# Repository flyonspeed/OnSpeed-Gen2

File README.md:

# OnSpeed-Gen2
Gen2 - OnSpeed open source hardware and software

This is a device that provides simple and intuitive Onspeed tone cues that allow the pilot to hear key performance AOA's as well outstanding progressive stall warning. ONSPEED AOA is used for approach and landing, assists with maximum performance takeoff and provides optimum turn performance.  The aural logic simplifies energy management and helps the pilot maintain positive aircraft control.

The current Gen2 device is avionics independent. The current features include:

    Measures differential pressures from an AOA pitot tube
  
    Measures static pressure
  
    Receives, parses and logs several types of EFIS data for testing purposes
  
    Receives, parses and logs flight test boom data for testing purposes
  
    Calculates a differential pressure based calibrated Angle of Attack and uses it to generate the OnSpeed tones.
  
    Can be wired directly into the aircraft's audio panel.
  
    It logs all data at 50Hz to the onboard SD card and provides an experimental AOA display via its Wifi interface.
  
    Logs can also be downloaded via Wifi.

We are happy to collaborate and answer any questions.  We will work with any experimenter or manufacturer that is interested in adapting the logic and always welcome qualified volunteers that want to join the project. Email us at team@flyonspeed.org to get in touch.

More details and videos of the OnSpeed system at http://flyOnspeed.org

**OnSpeed Gen2 System Diagram:**

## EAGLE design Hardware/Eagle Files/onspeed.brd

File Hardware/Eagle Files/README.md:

This folder contains the Onspeed Eagle files. Schematic and board files are also available in PDF form.\
\
**Note: We didn't end up using the Eagle .brd file. Board was rerouted in Altium. Gerber files and PDF of the board are in the Board Files folder**

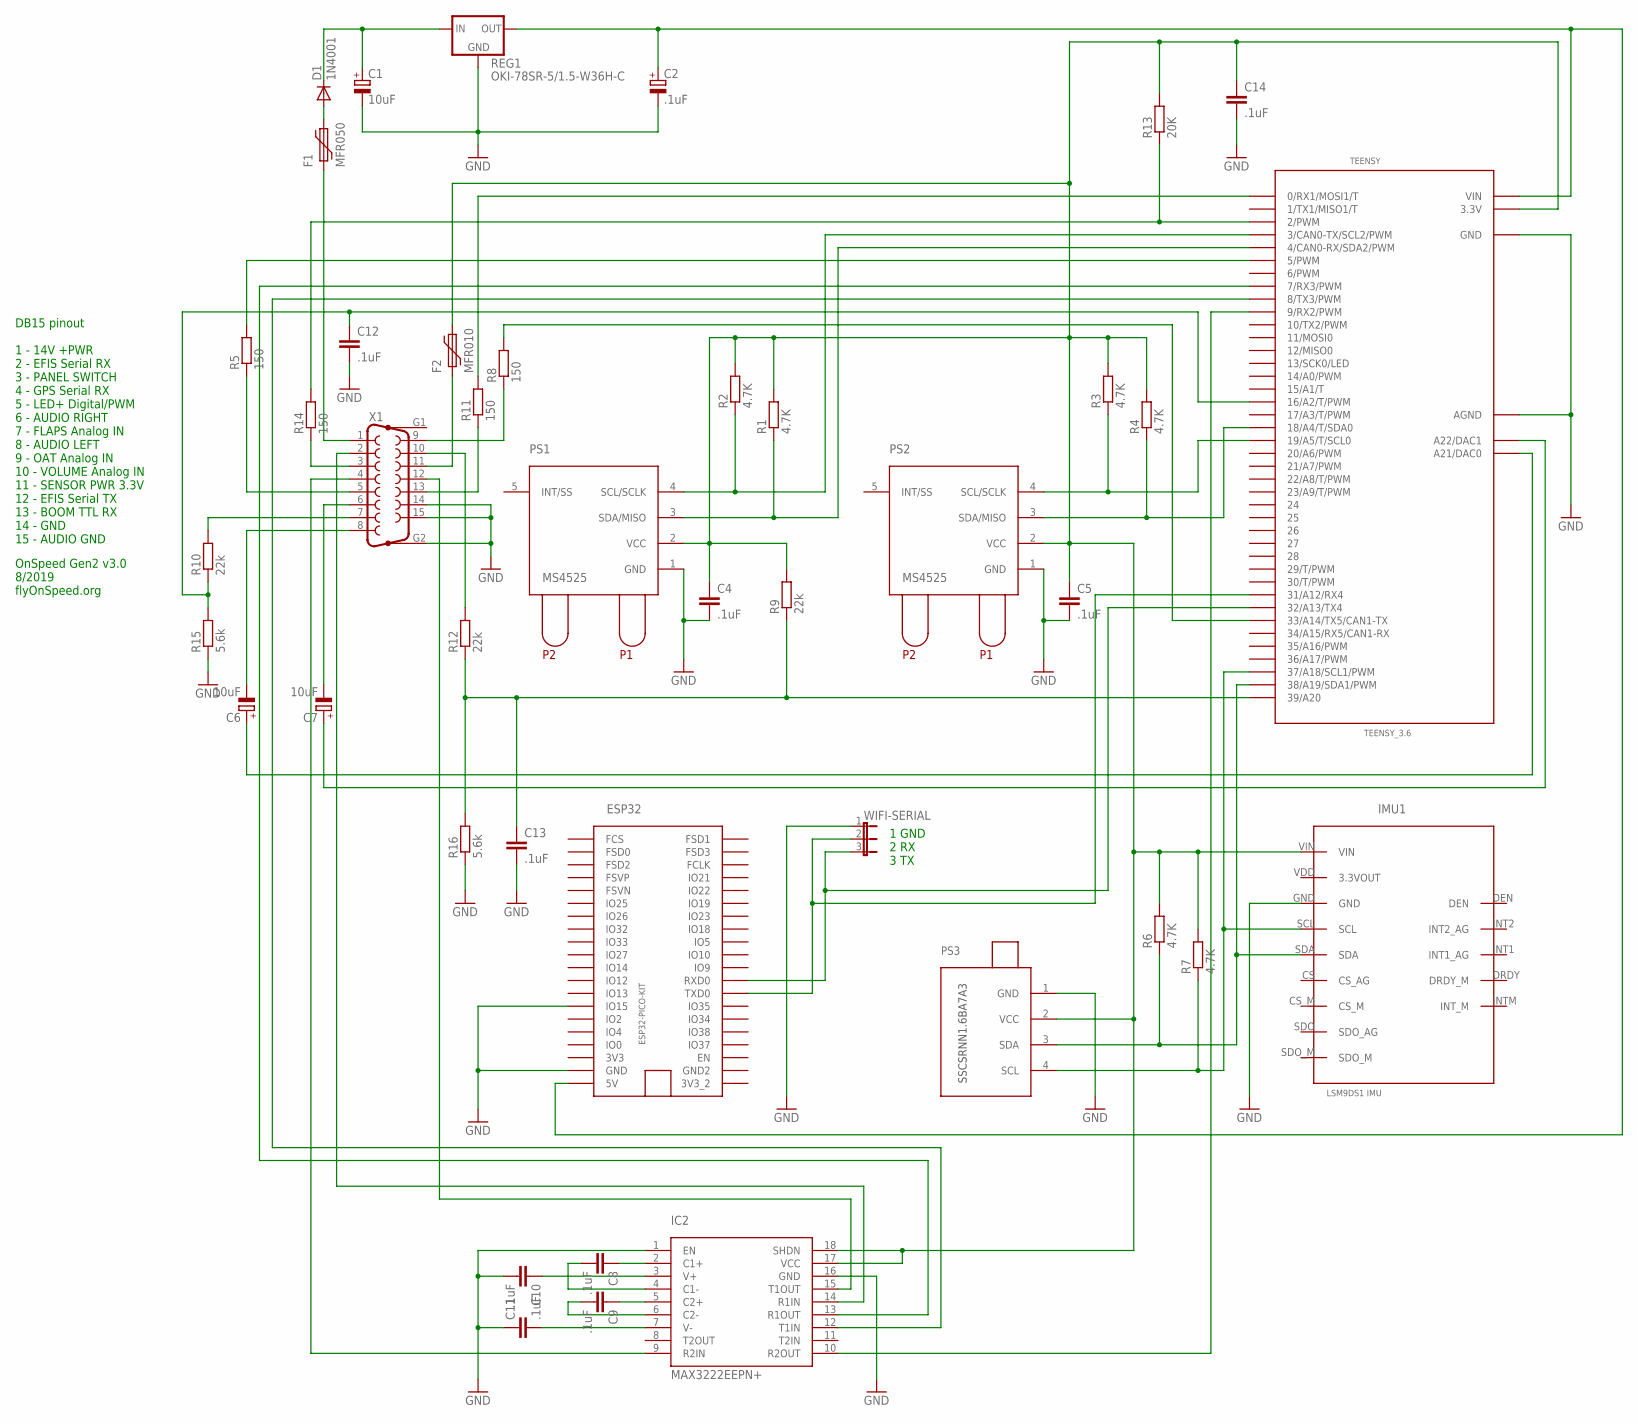
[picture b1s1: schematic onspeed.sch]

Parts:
C1, C6, C7: 10uF; E2-5
C2: .1uF; E2-5
C4, C5, C8, C9, C10, C11, C12, C13, C14: .1uF; C025-025X050
D1: 1N4001; DO41-10
ESP32: ESP32-PICO-KIT; ESP32PICOKIT
F1: MFR050; MF-5,1B
F2: MFR010; MF-5,1B
IC2: MAX3222EEPN+; DIL18
IMU1: LSM9DS1 IMU; LSM9DS1_BREAKOUT
PS1, PS2: MS4525; DIL08-500
PS3: SSCSRNN1.6BA7A3; SIP-RN
R1, R2, R3, R4, R6, R7: 4.7K; 0207/10
R5, R8, R11, R14: 150; 0207/10
R9, R10, R12: 22k; 0207/10
R13: 20K; 0207/10
R15, R16: 5.6k; 0207/10
REG1: OKI-78SR-5/1.5-W36H-C; SIP3H
TEENSY: TEENSY_3.6; TEENSY_3.6_DIL
WIFI-SERIAL: JP2E; JP2
X1: F15HP

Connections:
GND: C1.-, C2.-, C4.2, C5.2, C10.2, C11.1, C12.2, C13.2, C14.2, ESP32.P$GND (GND), ESP32.P$IO15 (IO15), IC2.1 (EN), IC2.16 (GND), IMU1.GND, PS1.1 (GND), PS2.1 (GND), PS3.1 (GND), R15.1, R16.1, REG1.2 (GND), TEENSY.AGND, TEENSY.GND, TEENSY.GND1 (GND), WIFI-SERIAL.1, X1.14, X1.15, X1.G2
unnamed: C1.+, D1.C, REG1.1 (IN)
unnamed: IC2.15 (T1OUT), X1.12
unnamed: R12.2, X1.10
unnamed: C2.+, ESP32.P$5V (5V), REG1.3 (OUT), TEENSY.VIN
unnamed: C12.1, R10.1, R15.2, TEENSY.16/A2 (16/A2/T/PWM)
unnamed: C7.-, X1.6
unnamed: R5.2, TEENSY.5 (5/PWM)
unnamed: IC2.12 (T1IN), TEENSY.8 (8/TX3/PWM)
unnamed: ESP32.P$RXD0 (RXD0), TEENSY.32/A13 (32/A13/TX4), WIFI-SERIAL.3
unnamed: ESP32.P$TXD0 (TXD0), TEENSY.31/A12 (31/A12/RX4), WIFI-SERIAL.2
unnamed: IC2.9 (R2IN), X1.4
unnamed: R11.2, TEENSY.0 (0/RX1/MOSI1/T)
unnamed: IC2.14 (R1IN), X1.2
unnamed: IC2.10 (R2OUT), TEENSY.9 (9/RX2/PWM)
unnamed: C7.+, TEENSY.A22 (A22/DAC1)
unnamed: PS1.4 (SCL/SCLK), R2.1, TEENSY.3 (3/CAN0-TX/SCL2/PWM)
unnamed: PS1.3 (SDA/MISO), R1.1, TEENSY.4 (4/CAN0-RX/SDA2/PWM)
unnamed: R8.2, TEENSY.33/A14 (33/A14/TX5/CAN1-TX)
unnamed: PS2.4 (SCL/SCLK), R3.1, TEENSY.19/A5 (19/A5/T/SCL0)
unnamed: D1.A, F1.2
unnamed: PS2.3 (SDA/MISO), R4.1, TEENSY.18/A4 (18/A4/T/SDA0)
unnamed: R13.1, R14.2, TEENSY.2 (2/PWM)
unnamed: C6.-, X1.8
unnamed: IC2.13 (R1OUT), TEENSY.7 (7/RX3/PWM)
unnamed: R8.1, X1.9
unnamed: C6.+, TEENSY.A21 (A21/DAC0)
unnamed: C8.2, IC2.4 (C1-)
unnamed: C13.1, R9.1, R12.1, R16.2, TEENSY.39/A20
unnamed: F1.1, X1.1
unnamed: C4.1, C5.1, C14.1, F2.2, IC2.17 (VCC), IC2.18 (SHDN), IMU1.VIN, PS1.2 (VCC), PS2.2 (VCC), PS3.2 (VCC), R1.2, R2.2, R3.2, R4.2, R6.2, R7.2, R9.2, R13.2, TEENSY.3.3V, TEENSY.3.3V3 (3.3V)
unnamed: C9.2, IC2.6 (C2-)
unnamed: F2.1, X1.11
unnamed: IMU1.SCL, PS3.4 (SCL), R7.1, TEENSY.37/A18 (37/A18/SCL1/PWM)
unnamed: IMU1.SDA, PS3.3 (SDA), R6.1, TEENSY.38/A19 (38/A19/SDA1/PWM)
unnamed: C11.2, IC2.7 (V-)
unnamed: R5.1, X1.5
unnamed: C10.1, IC2.3 (V+)
unnamed: C8.1, IC2.2 (C1+)
unnamed: C9.1, IC2.5 (C2+)
unnamed: R11.1, X1.13
unnamed: R10.2, X1.7
unnamed: R14.1, X1.3

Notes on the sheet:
DB15 pinout 1 - 14V +PWR 2 - EFIS Serial RX 3 - PANEL SWITCH 4 - GPS Serial RX 5 - LED+ Digital/PWM 6 - AUDIO RIGHT 7 - FLAPS Analog IN 8 - AUDIO LEFT 9 - OAT Analog IN 10 - VOLUME Analog IN 11 - SENSOR PWR 3.3V 12 - EFIS Serial TX 13 - BOOM TTL RX 14 - GND 15 - AUDIO GND
OnSpeed Gen2 v3.0 8/2019 flyOnSpeed.org
1 GND 2 RX 3 TX

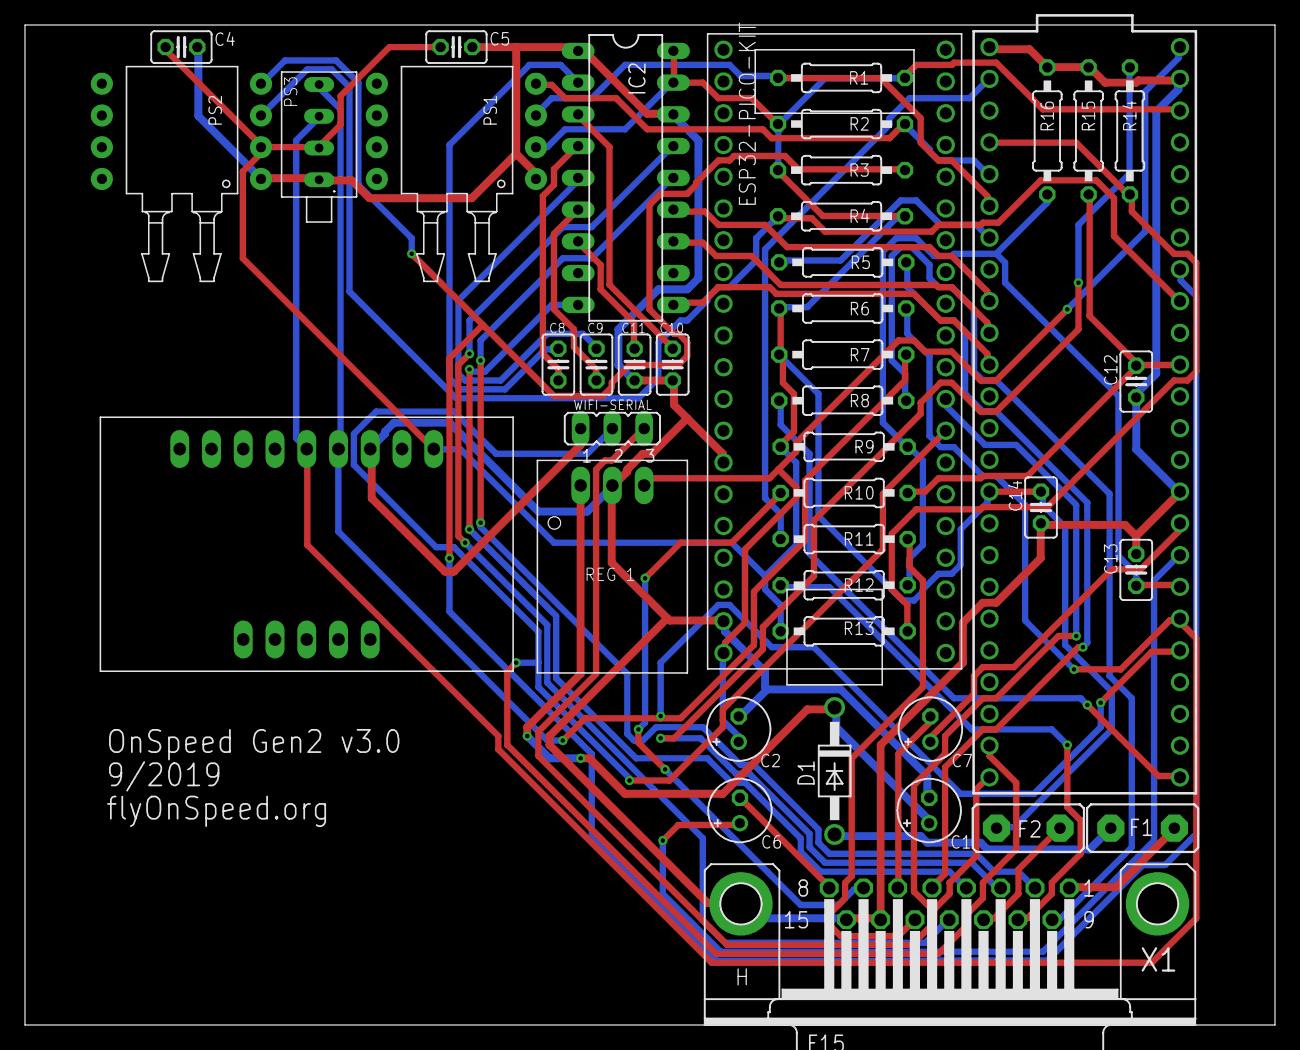
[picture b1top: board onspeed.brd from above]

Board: 2 copper layers, 100.0 x 80.0 mm, 42 parts (0 on the bottom side), 43 nets.

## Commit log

2019-10-28 Rename READE.me to README.md
2019-10-29 Add files via upload
    Fixed a tone glitch when transitioning from slow tone to warning tone.
    Updated RangeSweep mode code.
2020-02-29 Update to v3 code
    Updated software to latest v3 code and reorganized all folders to inlude al Arduino libraries in the proper location.
2020-02-29 deleted sdfat
2020-02-29 Added SdFat-beta
    Re-added SDFat library
2020-02-29 added Wire.h library
2020-02-29 Deleteed pubsubclient library. Not needed.
2020-02-29 removed unnecessary files
2020-03-24 fixed audio test
    fixed Left/Right channel audio test
2020-03-25 software update
    Teensy v3.0.3 and Wifi 3.0.5
2020-03-25 software update
    Teensy v3.0.3 and Wifi v3.0.5
2020-03-25 udpated Arduino libraries
2020-03-25 arduino libraries update
2020-05-23 Add files via upload
    Carlos made changes
2020-05-28 Update README.md
    updated Mouser parts list
2020-11-16 version update
    updated to version v3.1.5
    new version includes AHRS implementation using internal sensors.
2020-11-16 removed unused libraries
2021-01-13 fix watchdog from timing out during no load pressure read
2021-08-12 Update to version 3.2.1b
    Flight tested software. Calibration wizard and AHRS are work in progress.
    No need to compile wifi firmware, just upload OnSpeedWifi.ino.pico32.bin via the wifi firmware upgrade interface.
2021-08-12 v3.2.1b update
    Updated folder names to include version numbers
2021-08-27 folder name update
    Removed version from folder names
2021-08-27 removed version info from file names
    Removed version info from file names.
2021-12-10 Add files via upload
    better pin descriptions
2022-01-01 upgrade to v3.2.2.j, using updated
    upgrade to v3.2.2.j
    to be compiled on Arduino 1.8.16 & Teensyduino 1.55
2022-01-01 Create Extended_Kalam_Filter_with-alpha.m
    Added Matlab Kalman filter code for airspeed & baro corrected AHRS
2022-01-01 added Kalman Filter code
    added Matlab Kalman Filter code
2022-01-02 fixed #elif issue
    also updated Onspeed the Functions library
2022-01-05 Added M5 display code
    Added Arduino code for the M5 display. v3.2.2f
    To be compiled with ESP32 board library v2.0.
2022-01-27 update to version 3.2.2k
    Updated all 3 device software to the same version.
    Added NOBOOMCHECKSUM option to the Teensy code.
2022-02-12 Update README.md
    updated recommended SD card, this one is about twice as fast
2022-02-13 Add files via upload
    added compiled .bin file
2022-02-16 gaugewidgets
    add GaugeWidgets library
2022-02-16 added libraries
2022-02-16 M5 bin file
    M5 bin file, IAS in kts
2022-02-28 fixed SD card format
2022-02-28 M5 update
    serial detect fix
2022-03-25 efis based Calibration wizard
    Added ability to run calibration wizard using efis data
2022-06-03 ISM330DHCX IMU support
    Support for ISM330DHCX IMU (AHRS not yet tuned for new IMU)
2022-06-20 v3.2.2q
    Disabled the High pass filter on the ISM330 IMU
2022-06-25 Work on MGL parser
2022-06-25 Some fixes. If no message found fix. conversions fix.
2022-07-01 added debug info
2022-07-01 Updated version. debug fixes.
2022-07-02 add bad message debug msg.
2022-07-02 work on pulling out time string.
2022-07-02 fix for timestamp
2022-07-02 v3.2.2 AHRS code update
    Updated AHRS code for ISM330 IMU, updated iVSI code using complementary filter. Tuned to follow VN-300 performance.
2022-07-02 v3.2.3 update
2022-07-02 v3.2.3 wifi code update
2022-07-03 AHRS fix
2022-07-04 helper function warning cleanup
2022-07-04 fixes for outputting debug info.
2022-07-06 merged back new AHRS code v3.2.3
    also includes MGL parser with fixed warning messages
2022-07-06 fixed default define switches
2022-07-07 interrupt based push button, updated OneButton library
    DataMark glitch fixed
2022-07-11 fix for VSI
2022-07-11 IMU update.
2022-07-12 switch glitch fix
2022-07-14 fixed complementary VSI
2022-07-14 v 3.2.3d update
    tuned kalmanVSI filter
2022-07-14 v3.2.3d correction
2022-07-14 v3.2.3d VSI rate correction
2022-07-14 v3.2.3d VSI rate update #2
2022-07-16 v3.2.3e wifi file download improvements
2022-07-17 v3.2.3f fixed VSI
2022-07-18 added Wifi bin file
2022-07-19 v3.2.3g - Bob's MGL parser fix
2022-07-20 Added MGL engine and fuel data parsing.
2022-07-21 fixes.
2022-07-21 work on getting fuel
2022-07-21 commented out fuel for now.
2022-08-04 v3.2.3g1
    MGL parser fix for long messages
2022-08-10 3.2.3.g2
    MGL parser update
2022-08-10 v3.2.3.g3
    Bob's MGL parser fix and optimization
2022-09-25 v3.2.3 M5 display upgrade
    Fixed firmware upgrade prompt on M5 display
2022-12-05 upgrade to v3.3.0
    Fixed baro + IMU derived iVSI (needed for IMU calibration) and showing calibration data source on wifi display.
    AHRS output now consistent with VN-300.
2023-01-28 added OAT sensor
    1/28/2023 Added functionality to read digital OAT sensor DS18B20 on Pin 9. To enable uncomment the #define OAT_AVAILABLE line. Needs two new libraries: OneWire.h and DallasTemperature.h
2023-01-29 TAS formula, v3.3.1
    Fixed TAS formula
2023-01-29 v3.3.2 Fixed TAS formula
    Fixed TAS formula and added TAS to the logs.
2023-01-29 v3.3.2 TAS formula fix
    1/29/2023 Fixed TAS formula, and added TAS to the log file.
2023-03-01 v3.3.3. Adaptive pitch smoothing
    VERSION 3.3.3
    3/1/2023 Adaptive pitch filtering for smoother internal AHRS derived pitch angles, useful for IMU based calibration.
2023-03-05 Update onspeed_Gen2_v3_schematic.pdf
    Updated v3 schematic pinout. Same pinout just better pin descriptions.
2023-03-05 Updated onspeed_Gen2_v3_schematic.pdf
    Pinout description update.
2023-03-11 v3.3.4 fixed reboot issues and added high res analogread
    Fixed reboot on config load/save, and added HIGHRES_ANALOGREAD to have better resolution when reading volume and flap potentiometers
2023-03-12 v3.3.5 fixed error in adaptive smoothing
    v3.3.5 fixed error in adaptive smoothing.
2023-03-23 "v3.3.6"
    added capability to save screenshots of calibration results on the Wifi interface, and confirm before saving calibration to settings. (wifi code also updated)
2023-03-31 Externalized installation-specific config into local_config.h files for OnSpeedTeensy_AHRS & OnSpeedWifi
    - Moved installation-specific values to local_config.h files so the user doesn't have to hand-merge their local changes with project-wide changes for each software release.
    - Simplified the project-wide .gitignore file; changed version has same effect
2023-04-01 revert OnSpeedWifi calibration wizard variables to RV4 defaults
2023-04-01 replaced missing newline at end of OnSpeedWifi\local_config.h
2023-04-01 updated .gitignore to not include *.bak files in repository
2023-04-03 Replaced local_config.h with local_config-sample.h in AHRS & Wifi projects
    See the instructions at top of these files. Better approach to maintaining project-wide default version in the *-sample.h files, with installation-specific updates only being made in the local_config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
2023-04-03 Update .gitignore to exclude local_config.h files
    See instructions in the local_config-sampe.h files for intended usage.
2023-04-15 v3.3.7 TAS unit fix in AHRS
    fixed dumb mistake of using TAS in kts instead of m/sec in the AHRS airspeed correction when OAT enabled.
2023-04-15 v3.3.7a - optimized AHRS parameters
    optimized AHRS parameters for better pitch performance during AOA calibration
2023-04-17 v3.3.7 wifi upgrade
    Added timestamp column to the data log saved by the calibration wizard.
2023-08-26 v3.3.7 update
    v3.3.7 update
    separated serial display smoothing to Lateral & Vertical G.
2023-10-05 IMU axis definition fix for FWD/LEFT orientation
    v3.3.7g update
    10/5/23 Corrected Forward/Left orientation IMU axis defintion
2023-11-17 ventura update
    Mac Ventura & Arduino 2.0 ready
    don't forget to modify RX buffers for serial 1-4 after upgrading Teensyduino
2023-11-17 OAT sensor default to disabled
    OAT sensor default to disabled
